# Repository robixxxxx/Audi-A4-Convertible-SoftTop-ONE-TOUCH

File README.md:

# Audi A4 Convertible Soft Top ONE TOUCH Module
## 1. Basic module for opening the folding roof of an audi a4 convertible by double-clicking the button.

## 2. (work in progress) Module for opening the folding roof on audi a4 convertible by double-clicking the button or using the original remote control. The module is to have the ability to change the maximum speed at which the roof can be opened/closed.

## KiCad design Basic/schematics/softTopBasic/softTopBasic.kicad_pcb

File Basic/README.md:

# Audi A4 Convertible Soft Top Basic ONE TOUCH Module
This project provides an Arduino-based solution to control the roof of an Audi A4 Cabrio using original roof button. The provided code manages the open and close operations of the roof by double-click .

## 1. Hardware Requirements
- Arduino board (e.g., Arduino Uno)
- Two BC547 transistors
- Two 1kOhm resistors
- Connecting wires
- Male goldpin 2x3
- Female golpin 2x3

### The wiring diagram is available in the schematics folder

## 2. Software

### Installation
1. Install the [Visual Studio Code](https://code.visualstudio.com) with [PlatformIO](https://platformio.org) extension or [Arduino IDE](https://www.arduino.cc/en/software)
2. Connect your Arduino board to your computer via USB.
3. Open IDE and clone repository or create a new project and copy the code
5. Verify and upload the code to your Arduino

### Functionality
- Button Debouncing: Prevents false triggering of button presses.
- Button Sequence Handling: Manages the sequence of button presses to ensure the correct operation of the roof.
- Safety Timeout: Automatically stops the roof if it moves beyond the predefined time.
### Usage
- Opening the Roof: Press the "Open" button twice within 800ms to start opening the roof. Pressing the button more than twice will stop the roof.
- Closing the Roof: Press the "Close" button twice within 800ms to start closing the roof. Pressing the button more than twice will stop the roof.
## Ensure the vehicle is parked and it is safe to operate the roof before using this system.

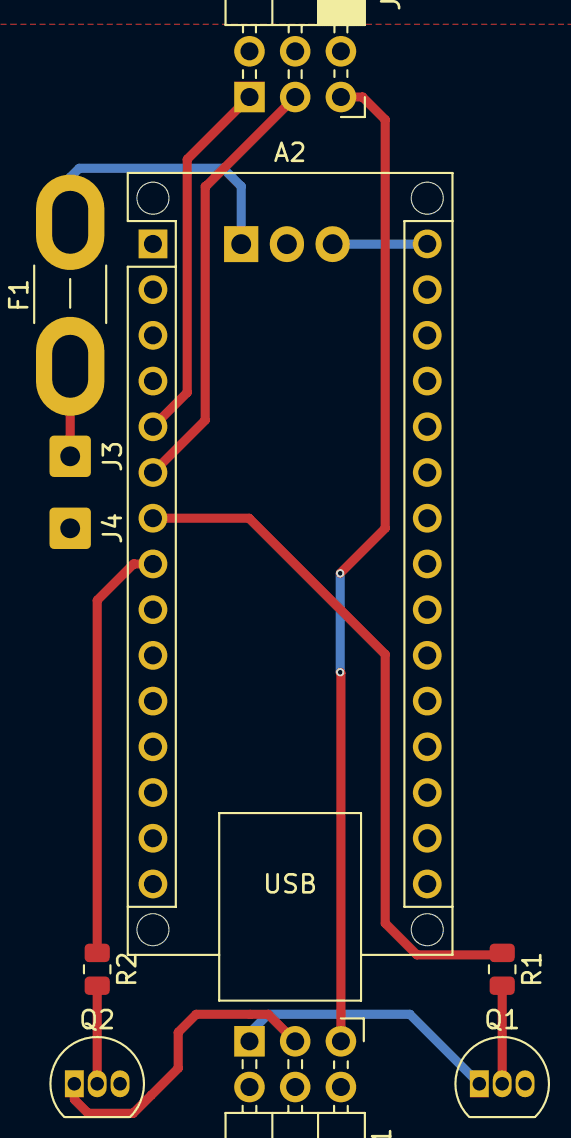
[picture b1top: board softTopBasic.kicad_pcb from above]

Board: 2 copper layers, 11 parts (1 on the bottom side), 13 nets.

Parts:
A2: Arduino_Nano_Every; Arduino_Nano_WithMountingHoles
F1: 150mA; Fuse_Blade_Mini_directSolder
J1: Original Plug; PinHeader_2x03_P2.54mm_Horizontal
J2: New Switch Plug; PinSocket_2x03_P2.54mm_Horizontal
J3: +12V; SolderWire-0.5sqmm_1x01_D0.9mm_OD2.3mm
J4: GND; SolderWire-0.5sqmm_1x01_D0.9mm_OD2.3mm
Q1, Q2: BC547; TO-92_Inline
R1, R2: 1k; R_0805_2012Metric
U1: LM7805_TO220; TO-220-3_Vertical

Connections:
+5V: A2.30 (VIN), U1.3 (VO)
+12V: F1.2, U1.1 (VI)
/INPUT1: A2.5 (D2), J2.1
/INPUT2: A2.6 (D3), J2.2
/Inputs/button illumination: J1.3, J2.3
/OUTPUT1: A2.7 (D4), R1.1
/OUTPUT2: A2.8 (D5), R2.1
GND: A2.4 (GND), A2.29 (GND), J1.4, J2.4, J4.1, Q1.3 (E), Q2.3 (E), U1.2 (GND)
unnamed: J1.1, Q1.1 (C)
unnamed: J1.2, Q2.1 (C)
unnamed: F1.1, J3.1
unnamed: Q1.2 (B), R1.2
unnamed: Q2.2 (B), R2.2

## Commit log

2024-05-06 new file: .gitignore new file: .vscode/extensions.json new file: include/README new file: lib/README new file: platformio.ini new file: src/SoftTop.code-workspace new file: src/main.cpp new file: tes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
2024-05-15 modified: platformio.ini modified: src/main.cpp
2024-06-04 renamed: .vscode/extensions.json -> Basic/.vscode/extensions.json renamed: include/README -> Basic/include/README renamed: lib/README -> Basic/lib/README renamed: platformio.ini -> Basic/platformio.i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
2024-06-04 new file: Basic/README.md new file: README.md modified: Smart/README.md
2024-06-04 modified: README.md
2024-06-06 modified: Basic/README.md
